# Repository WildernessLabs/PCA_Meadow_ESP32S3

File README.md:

# PCA_Meadow_ESP32S3
Meadow PCB using the ESP32 S3

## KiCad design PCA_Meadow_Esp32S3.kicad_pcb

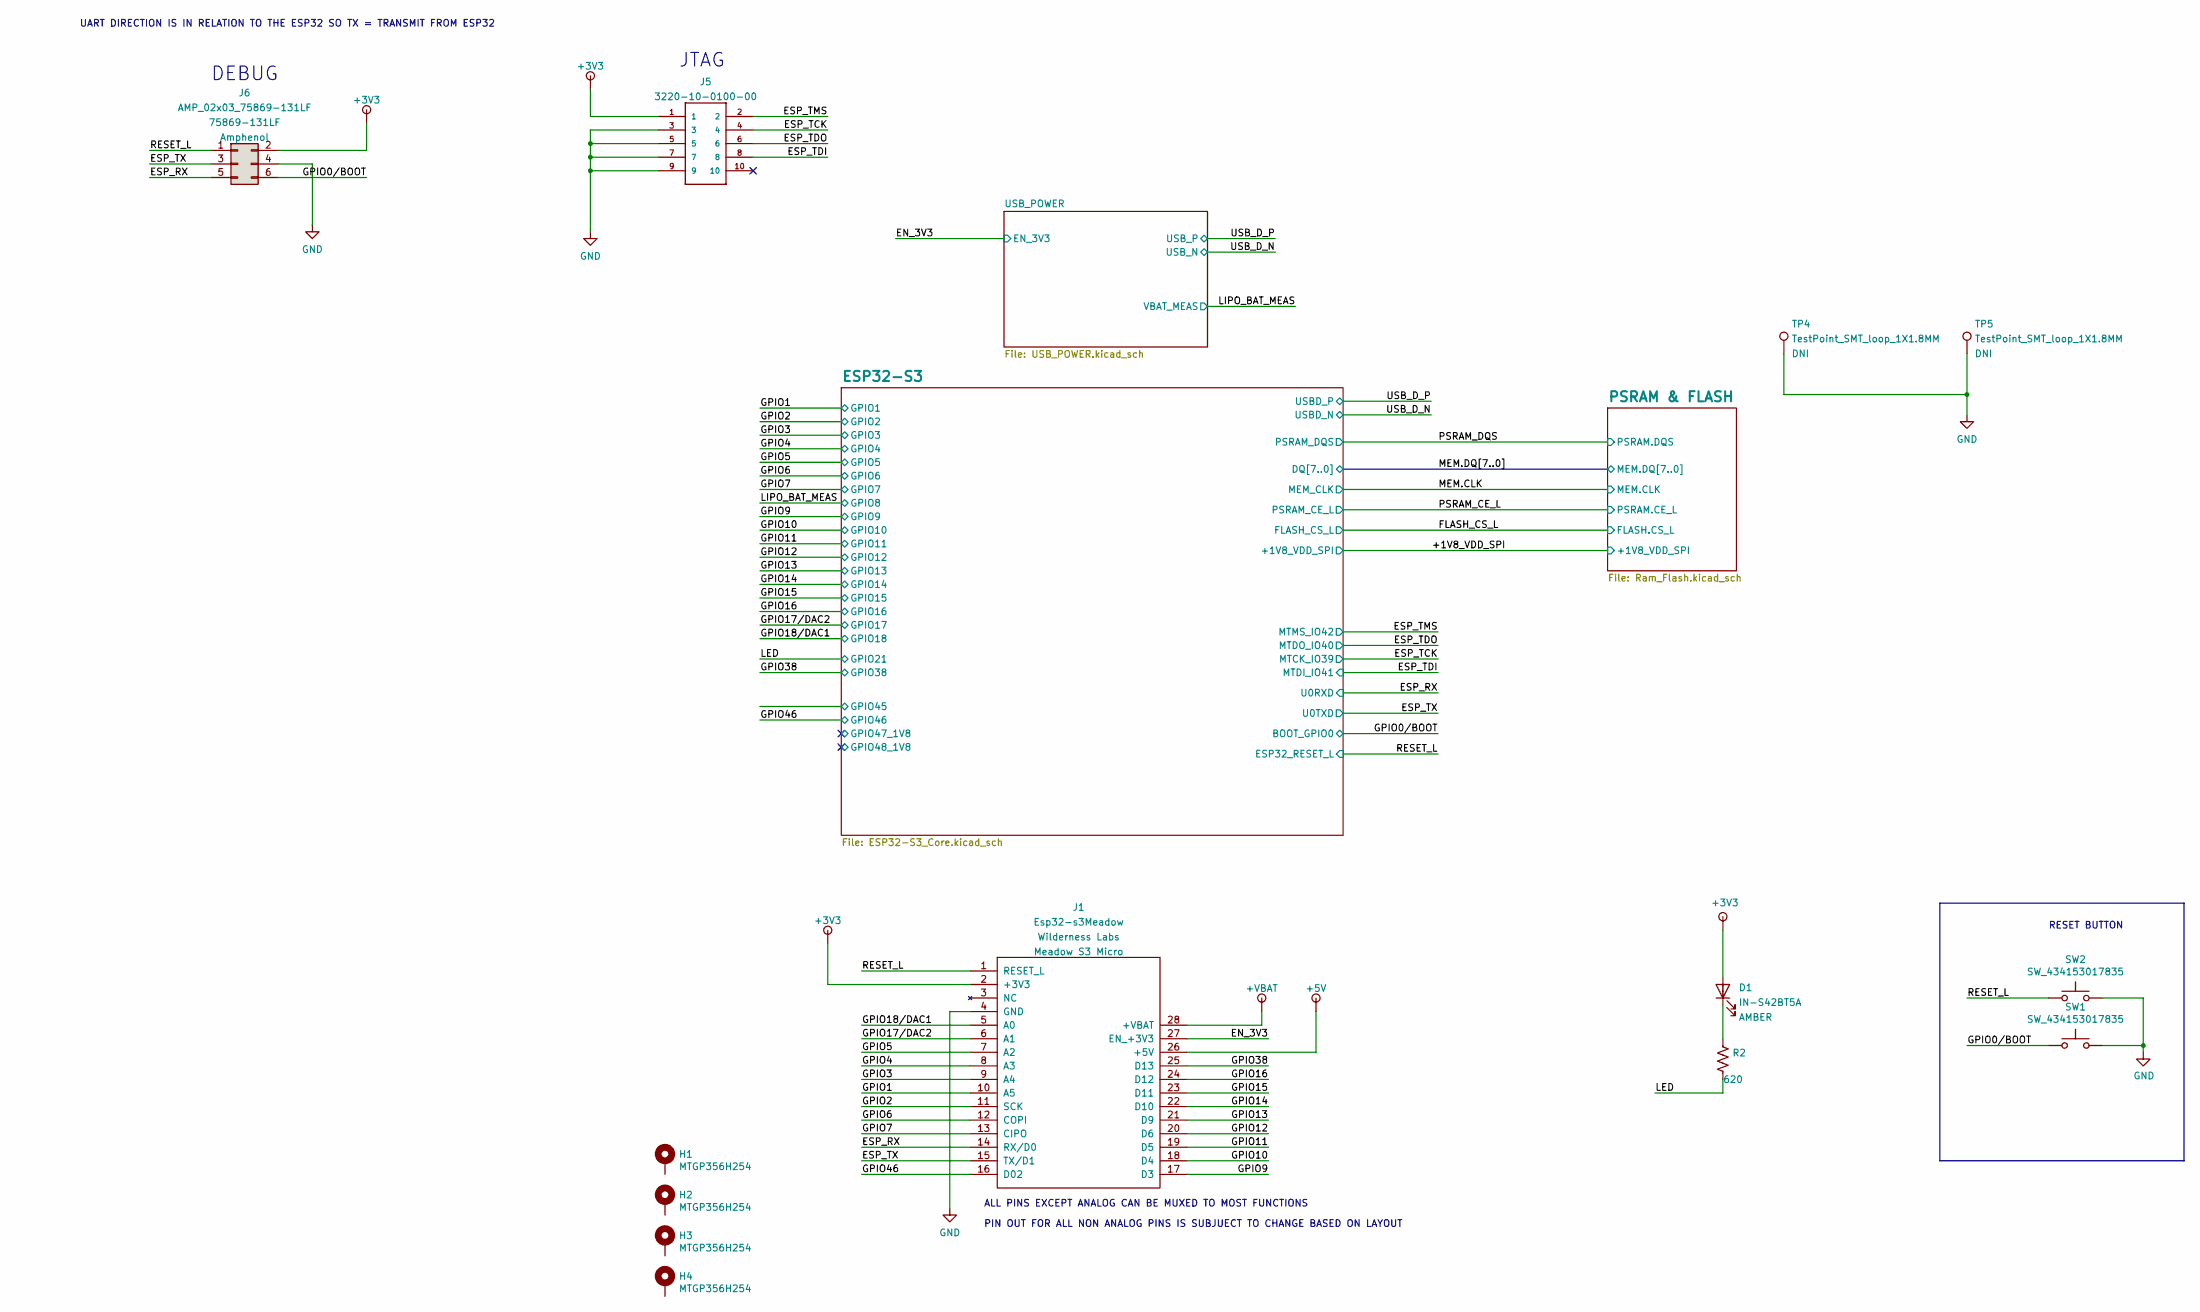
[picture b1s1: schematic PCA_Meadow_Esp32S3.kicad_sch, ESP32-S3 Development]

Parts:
D1: LED_A_IN-S42BT5A; LED_0402
H1, H2, H3, H4: MTGP356H254
J1: Esp32-s3Meadow; WL_S3_MicroMeadow
J5: CNC-3220-10-0100-00; CNC_3220-10-0100-00
J6: AMP_02x03_75869-131LF; Amphenol_75869-131LF
R2: R_620_1%_0201; R_0201
SW1, SW2: SW_434153017835; WURTH_434153017835
TP4, TP5: TestPoint_SMT_loop_1X1.8MM; TP_S2761-46R

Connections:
+3V3: D1.1 (A), J1.2 (+3V3), J5.1, J6.2; also elsewhere on the board
+5V: J1.26 (+5V); also elsewhere on the board
+VBAT: J1.28 (+VBAT); also elsewhere on the board
/EN_3V3: J1.27 (EN_+3V3); also elsewhere on the board
/ESP_RX: J1.14 (RX/D0), J6.5; also elsewhere on the board
/ESP_TCK: J5.4; also elsewhere on the board
/ESP_TDI: J5.8; also elsewhere on the board
/ESP_TDO: J5.6; also elsewhere on the board
/ESP_TMS: J5.2; also elsewhere on the board
/ESP_TX: J1.15 (TX/D1), J6.3; also elsewhere on the board
/GPIO0/BOOT: J6.6, SW1.1, SW1.3; also elsewhere on the board
/GPIO1: J1.10 (A5); also elsewhere on the board
/GPIO2: J1.11 (SCK); also elsewhere on the board
/GPIO3: J1.9 (A4); also elsewhere on the board
/GPIO4: J1.8 (A3); also elsewhere on the board
/GPIO5: J1.7 (A2); also elsewhere on the board
/GPIO6: J1.12 (COPI); also elsewhere on the board
/GPIO7: J1.13 (CIPO); also elsewhere on the board
/GPIO9: J1.17 (D3); also elsewhere on the board
/GPIO10: J1.18 (D4); also elsewhere on the board
/GPIO11: J1.19 (D5); also elsewhere on the board
/GPIO12: J1.20 (D6); also elsewhere on the board
/GPIO13: J1.21 (D9); also elsewhere on the board
/GPIO14: J1.22 (D10); also elsewhere on the board
/GPIO15: J1.23 (D11); also elsewhere on the board
/GPIO16: J1.24 (D12); also elsewhere on the board
/GPIO17/DAC2: J1.6 (A1); also elsewhere on the board
/GPIO18/DAC1: J1.5 (A0); also elsewhere on the board
/GPIO38: J1.25 (D13); also elsewhere on the board
/GPIO46: J1.16 (D02); also elsewhere on the board
/LED: R2.2; also elsewhere on the board
/RESET_L: J1.1 (RESET_L), J6.1, SW2.1, SW2.3; also elsewhere on the board
GND: J1.4 (GND), J5.3, J5.5, J5.7, J5.9, J6.4, SW1.2, SW1.4, SW2.2, SW2.4, TP4.1, TP5.1; also elsewhere on the board
unnamed: D1.2 (K), R2.1

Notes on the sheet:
UART DIRECTION IS IN RELATION TO THE ESP32 SO TX = TRANSMIT FROM ESP32
DEBUG
JTAG
RESET BUTTON
PIN OUT FOR ALL NON ANALOG PINS IS SUBJUECT TO CHANGE BASED ON LAYOUT
ALL PINS EXCEPT ANALOG CAN BE MUXED TO MOST FUNCTIONS

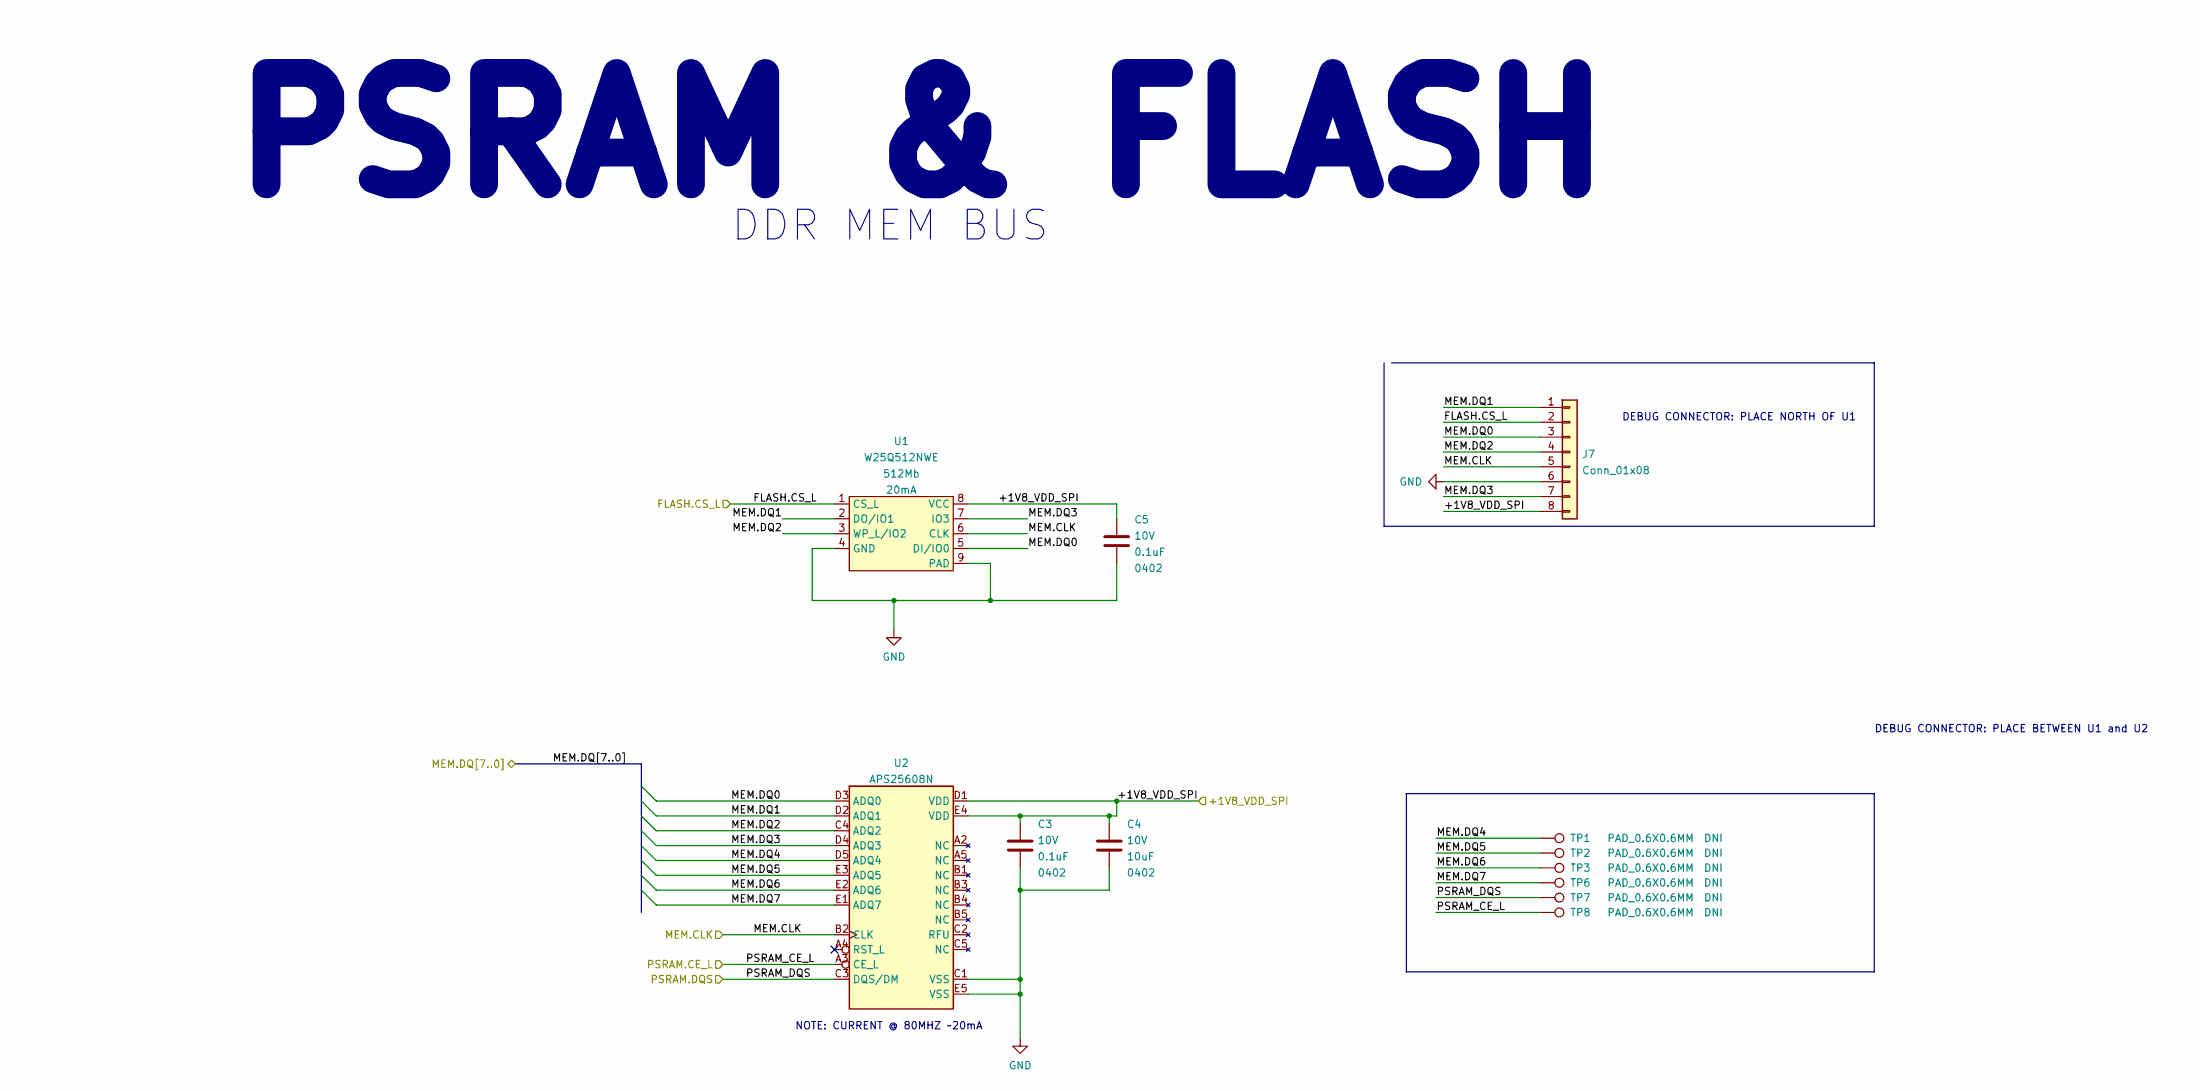
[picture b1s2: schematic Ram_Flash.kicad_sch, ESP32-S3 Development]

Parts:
C3, C5: C_0402_0.1UF_10V_X5R; C_0402_1005Metric; Voltage 10V; Tolerance 20%
C4: C_0402_10UF_10V_X5R; C_0402_1005Metric; Voltage 10V; Tolerance 20%
J7: Conn_01x08; PinHeader_2x04_P2.54mm_Vertical
TP1, TP2, TP3, TP6, TP7, TP8: PAD_0.6X0.6MM; PAD_SQ_0.6X0.6MM
U1: W25Q512NWE; WSON-8-1EP_6x8mm_P1.27mm_EP3.4x4.3mm; VOLTAGE 1.8V
U2: APS25608N; BGA24C100P5X5_800X600X120N

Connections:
/+1V8_VDD_SPI: C3.1, C4.1, C5.1, J7.8, U1.8 (VCC), U2.D1 (VDD), U2.E4 (VDD); also elsewhere on the board
/FLASH_CS_L: J7.2, U1.1 (CS_L); also elsewhere on the board
/MEM.CLK: J7.5, U1.6 (CLK), U2.B2 (CLK); also elsewhere on the board
/MEM.DQ0: J7.3, U1.5 (DI/IO0), U2.D3 (ADQ0); also elsewhere on the board
/MEM.DQ1: J7.1, U1.2 (DO/IO1), U2.D2 (ADQ1); also elsewhere on the board
/MEM.DQ2: J7.4, U1.3 (WP_L/IO2), U2.C4 (ADQ2); also elsewhere on the board
/MEM.DQ3: J7.7, U1.7 (IO3), U2.D4 (ADQ3); also elsewhere on the board
/MEM.DQ4: TP1.1, U2.D5 (ADQ4); also elsewhere on the board
/MEM.DQ5: TP2.1, U2.E3 (ADQ5); also elsewhere on the board
/MEM.DQ6: TP3.1, U2.E2 (ADQ6); also elsewhere on the board
/MEM.DQ7: TP6.1, U2.E1 (ADQ7); also elsewhere on the board
/PSRAM_CE_L: TP8.1, U2.A3 (CE_L); also elsewhere on the board
/PSRAM_DQS: TP7.1, U2.C3 (DQS/DM); also elsewhere on the board
GND: C3.2, C4.2, C5.2, J7.6, U1.4 (GND), U1.9 (PAD), U2.C1 (VSS), U2.E5 (VSS); also elsewhere on the board

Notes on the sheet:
DEBUG CONNECTOR: PLACE BETWEEN U1 and U2
DEBUG CONNECTOR: PLACE NORTH OF U1
NOTE: CURRENT @ 80MHZ ~20mA
PSRAM & FLASH
DDR MEM BUS

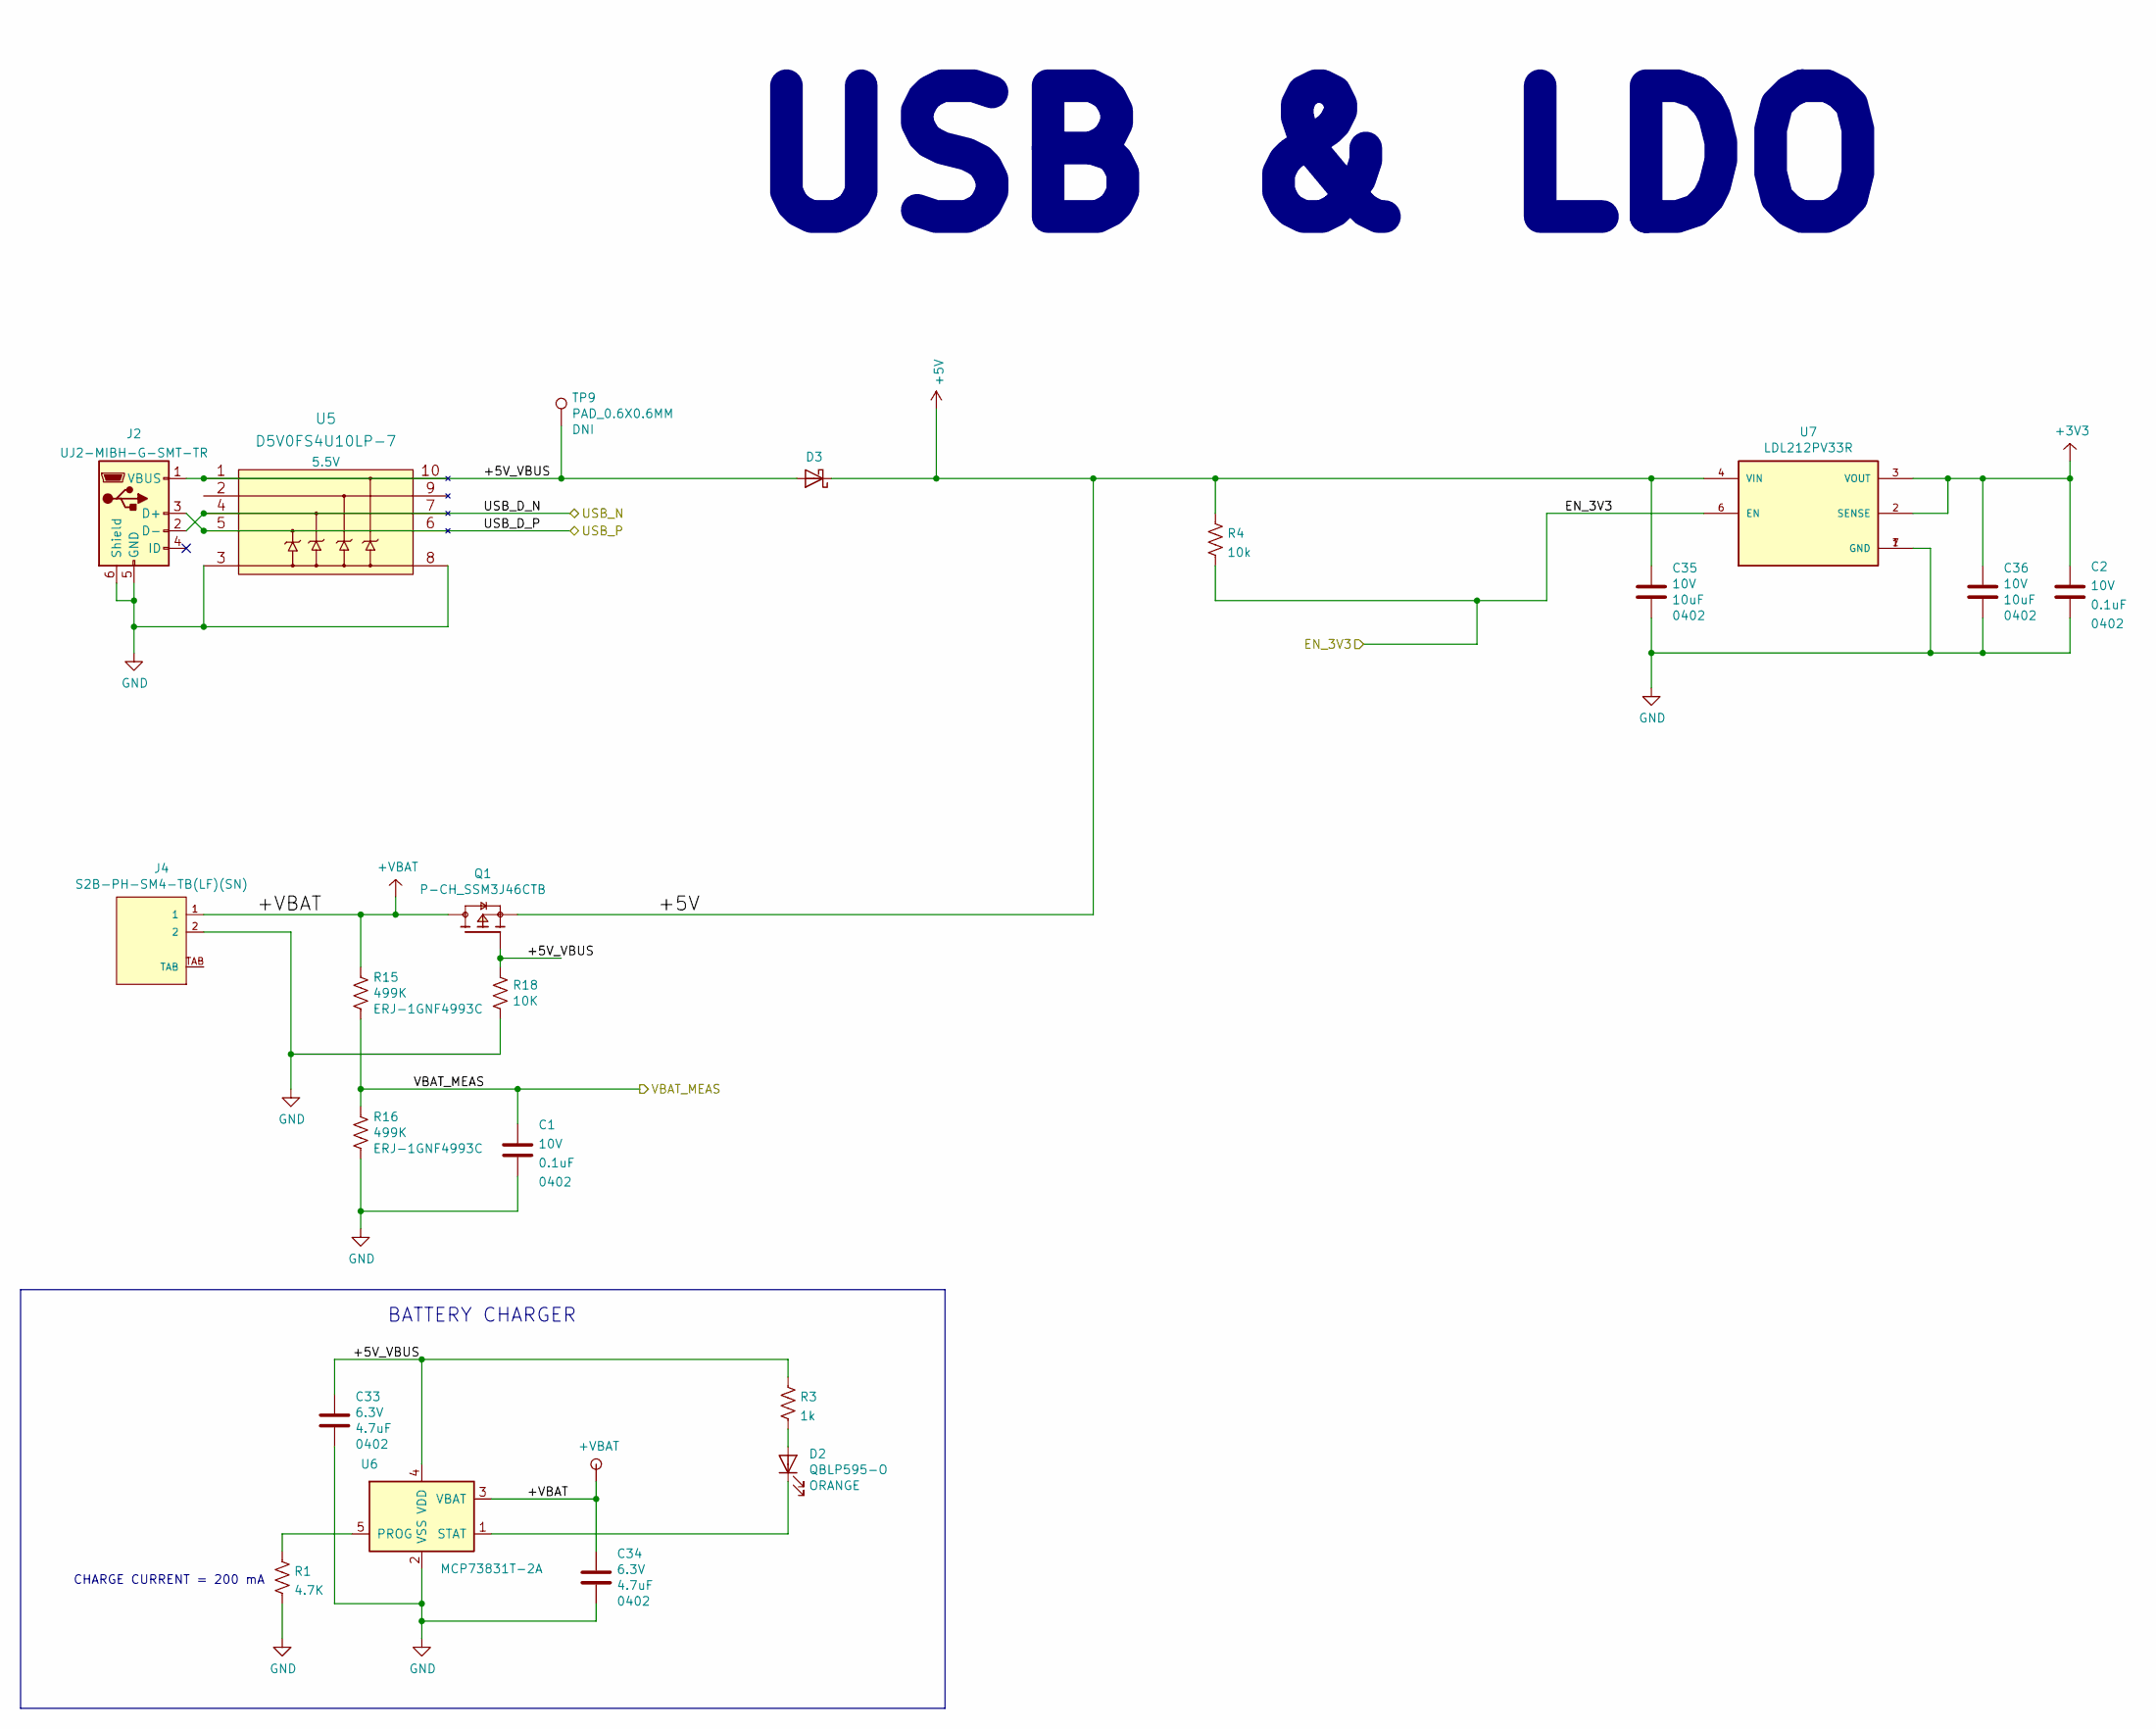
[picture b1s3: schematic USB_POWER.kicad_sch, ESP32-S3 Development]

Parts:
C1, C2: C_0402_0.1UF_10V_X5R; C_0402_1005Metric; Voltage 10V; Tolerance 20%
C33, C34: C_0402_4.7UF_10V_X5R_10%; C_0402_1005Metric; Voltage 6.3V; Tolerance 10%
C35, C36: C_0402_10UF_10V_X5R; C_0402_1005Metric; Voltage 10V; Tolerance 20%
D2: LED_O_QBLP595-O; LED_0402
D3: BAT60A; D_SOD-323
J2: USB_B_MicroCUI; USB_Micro-B_CUI_UJ2-MIBH-G
J4: S2B-PH-SM4-TB(LF)(SN); JST_S2B-PH-SM4-TB(LF)(SN)
Q1: P-CH_SSM3J46CTB; CST3b_TOS
R1: R_4K7_1%_0402; R_0402_1005Metric
R3: R_1K_1%_0402; R_0402_1005Metric; Tolerance 1%
R4: R_10k_1%_0603; R_0603; Tolerance 1%
R15, R16: R_499K_1%_0201; R_0201
R18: R_10K_1%_0201; R_0201
TP9: PAD_0.6X0.6MM; PAD_SQ_0.6X0.6MM
U5: D5V0FS4U10LP-7; U-DFN2510_1X2P5_DIO; Voltage 5.5V
U6: MCP73831T-2A; SOT-23-5
U7: LDL212PV33R; SON50P200X200X80-7N

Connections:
+3V3: C2.1, C36.1, U7.2 (SENSE), U7.3 (VOUT); also elsewhere on the board
+5V: C35.1, D3.1 (K), Q1.2 (SOURCE), R4.1, U7.4 (VIN); also elsewhere on the board
+VBAT: C34.1, J4.1, Q1.3 (DRAIN), R15.1, U6.3 (VBAT); also elsewhere on the board
/EN_3V3: R4.2, U7.6 (EN); also elsewhere on the board
/LIPO_BAT_MEAS: C1.1, R15.2, R16.1; also elsewhere on the board
/USB_D_N: J2.2 (D-), U5.4; also elsewhere on the board
/USB_D_P: J2.3 (D+), U5.5; also elsewhere on the board
/USB_POWER/+5V_VBUS: C33.1, D3.2 (A), J2.1 (VBUS), Q1.1 (GATE), R3.1, R18.1, TP9.1, U5.1, U6.4 (VDD)
GND: C1.2, C2.2, C33.2, C34.2, C35.2, C36.2, J2.5 (GND), J2.6 (Shield), J4.2, R1.2, R16.2, R18.2, U5.3 (VSS), U5.8 (VSS), U6.2 (VSS), U7.1 (GND), U7.7 (GND); also elsewhere on the board
unnamed: D2.1 (A), R3.2
unnamed: D2.2 (K), U6.1 (STAT)
unnamed: R1.1, U6.5 (PROG)

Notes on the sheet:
CHARGE CURRENT = 200 mA
USB & LDO
BATTERY CHARGER

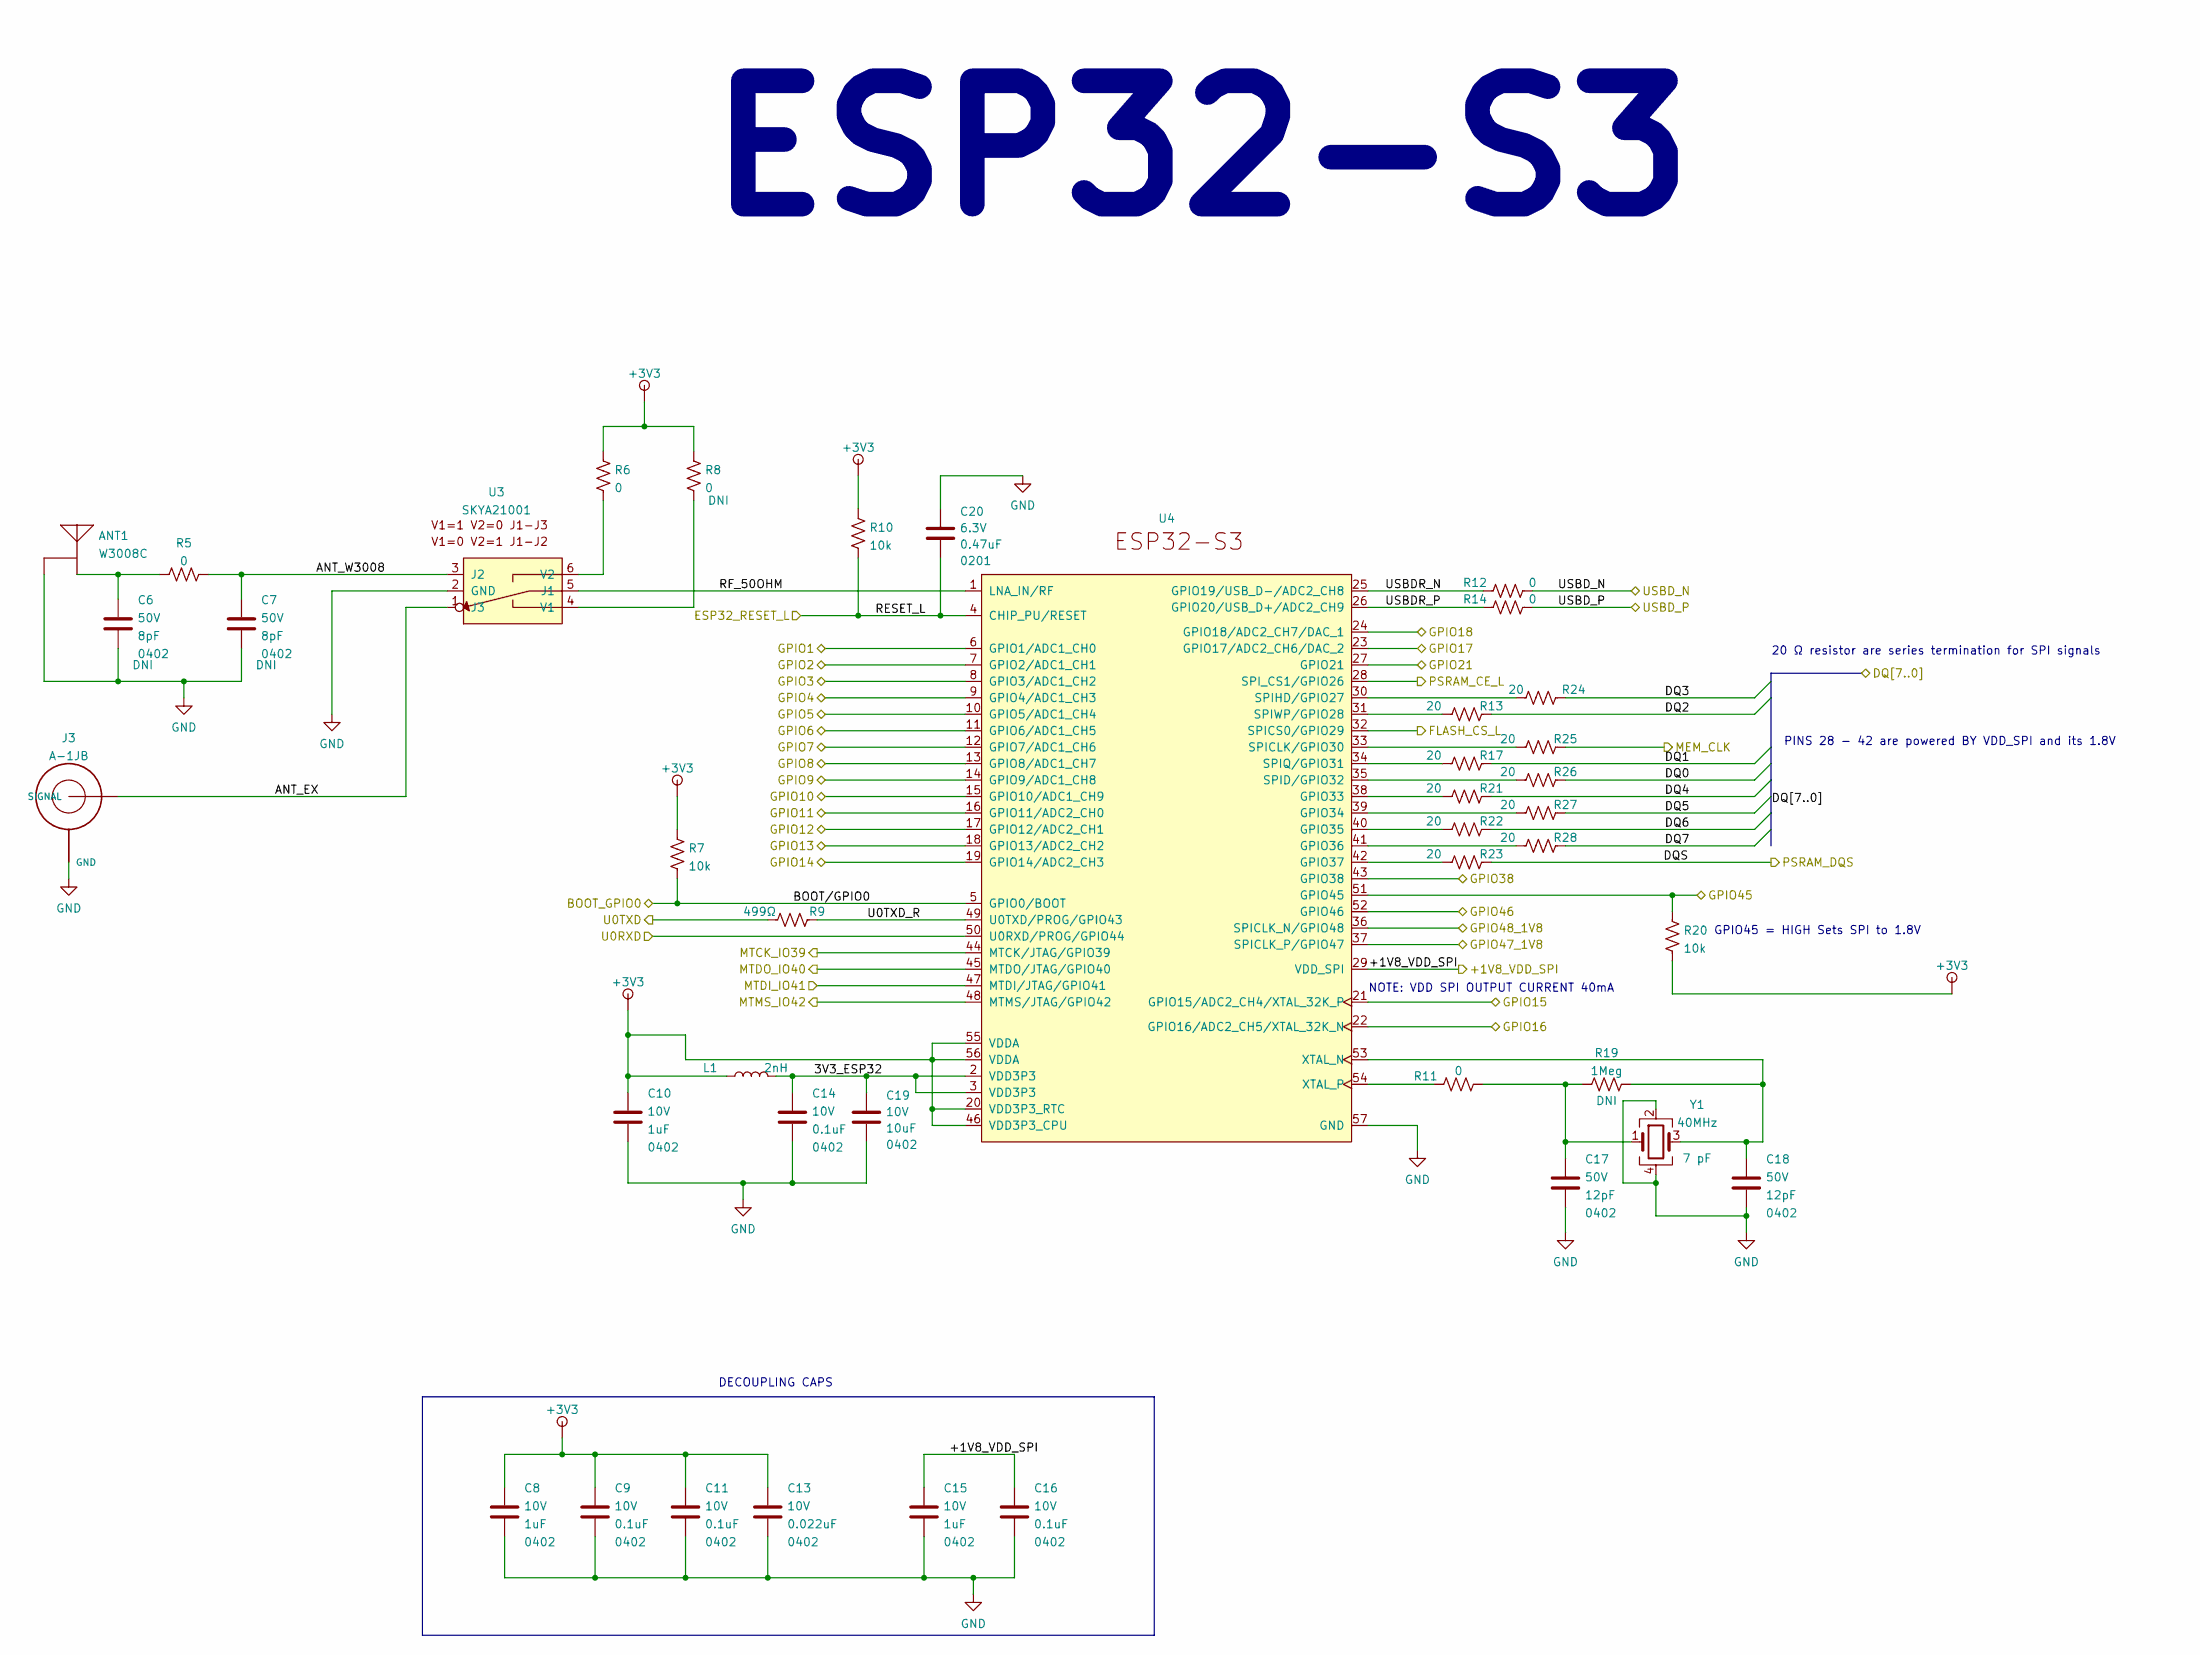
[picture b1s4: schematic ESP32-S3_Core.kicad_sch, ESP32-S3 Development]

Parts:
ANT1: W3008C; ANTENNA_W3008C
C6, C7: C_0402_8pF_50V_X5R; C_0402_1005Metric; Voltage 50V; Tolerance 0.25pF
C8, C10, C15: C_0402_1UF_10V_X5R; C_0402_1005Metric; Voltage 10V; Tolerance 20%
C9, C11, C14, C16: C_0402_0.1UF_10V_X5R; C_0402_1005Metric; Voltage 10V; Tolerance 20%
C13: C_0402_0.022UF_50V_X5R; C_0402_1005Metric; Voltage 10V; Tolerance 10%
C17, C18: C_0402_12pF_50V_X5R; C_0402_1005Metric; Voltage 50V; Tolerance 5%
C19: C_0402_10UF_10V_X5R; C_0402_1005Metric; Voltage 10V; Tolerance 20%
C20: C_0201_0.47UF_6.3V_X5R; C_0201; Voltage 6.3V; Tolerance 10%
J3: A-1JB; AMPHENOL_A-1JB
L1: L_0402_2nH_50mΩ; L_0402; I Rating 1A; PartValue 2nH
R5, R11, R12, R14: R_0_1%_0402; R_0402_1005Metric
R6, R8: R_0R_1%_0603; R_0603; Tolerance 1%
R7, R10, R20: R_10k_1%_0603; R_0603; Tolerance 1%
R9: R_499R_1%_0603; R_0603; Tolerance 1%
R13, R17, R21, R22, R23, R24, R25, R26, R27, R28: R_20_1%_0402; R_0402_1005Metric
R19: R_1M_1%_0402; R_0402_1005Metric
U3: SKYA21001; SOT-363_SC-70-6
U4: ESP32-S3; QFN-56_EP_7x7_Pitch0.4mm
Y1: ABM12W-40.0000MHZ-7-B1U-T3; XTAL_ABM12W-24.0000MHZ-6-B1U-T3

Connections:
+3V3: C8.1, C9.1, C10.1, C11.1, C13.1, L1.1, R6.1, R7.1, R8.1, R10.1, R20.2, U4.20 (VDD3P3_RTC), U4.46 (VDD3P3_CPU), U4.55 (VDDA), U4.56 (VDDA); also elsewhere on the board
/+1V8_VDD_SPI: C15.1, C16.1, U4.29 (VDD_SPI); also elsewhere on the board
/ESP32-S3/3V3_ESP32: C14.1, C19.1, L1.2, U4.2 (VDD3P3), U4.3 (VDD3P3)
/ESP32-S3/ANT_EX: J3.SIGNAL, U3.1 (J3)
/ESP32-S3/ANT_W3008: C7.1, R5.2, U3.3 (J2)
/ESP32-S3/GPIO45: R20.1, U4.51 (GPIO45)
/ESP32-S3/GPIO47_1V8: U4.37 (SPICLK_P/GPIO47)
/ESP32-S3/GPIO48_1V8: U4.36 (SPICLK_N/GPIO48)
/ESP32-S3/RF_50OHM: U3.5 (J1), U4.1 (LNA_IN/RF)
/ESP32-S3/U0TXD_R: R9.2, U4.49 (U0TXD/PROG/GPIO43)
/ESP32-S3/USBDR_N: R12.1, U4.25 (GPIO19/USB_D-/ADC2_CH8)
/ESP32-S3/USBDR_P: R14.1, U4.26 (GPIO20/USB_D+/ADC2_CH9)
/ESP_RX: U4.50 (U0RXD/PROG/GPIO44); also elsewhere on the board
/ESP_TCK: U4.44 (MTCK/JTAG/GPIO39); also elsewhere on the board
/ESP_TDI: U4.47 (MTDI/JTAG/GPIO41); also elsewhere on the board
/ESP_TDO: U4.45 (MTDO/JTAG/GPIO40); also elsewhere on the board
/ESP_TMS: U4.48 (MTMS/JTAG/GPIO42); also elsewhere on the board
/ESP_TX: R9.1; also elsewhere on the board
/FLASH_CS_L: U4.32 (SPICS0/GPIO29); also elsewhere on the board
/GPIO0/BOOT: R7.2, U4.5 (GPIO0/BOOT); also elsewhere on the board
/GPIO1: U4.6 (GPIO1/ADC1_CH0); also elsewhere on the board
/GPIO2: U4.7 (GPIO2/ADC1_CH1); also elsewhere on the board
/GPIO3: U4.8 (GPIO3/ADC1_CH2); also elsewhere on the board
/GPIO4: U4.9 (GPIO4/ADC1_CH3); also elsewhere on the board
/GPIO5: U4.10 (GPIO5/ADC1_CH4); also elsewhere on the board
/GPIO6: U4.11 (GPIO6/ADC1_CH5); also elsewhere on the board
/GPIO7: U4.12 (GPIO7/ADC1_CH6); also elsewhere on the board
/GPIO9: U4.14 (GPIO9/ADC1_CH8); also elsewhere on the board
/GPIO10: U4.15 (GPIO10/ADC1_CH9); also elsewhere on the board
/GPIO11: U4.16 (GPIO11/ADC2_CH0); also elsewhere on the board
/GPIO12: U4.17 (GPIO12/ADC2_CH1); also elsewhere on the board
/GPIO13: U4.18 (GPIO13/ADC2_CH2); also elsewhere on the board
/GPIO14: U4.19 (GPIO14/ADC2_CH3); also elsewhere on the board
/GPIO15: U4.21 (GPIO15/ADC2_CH4/XTAL_32K_P); also elsewhere on the board
/GPIO16: U4.22 (GPIO16/ADC2_CH5/XTAL_32K_N); also elsewhere on the board
/GPIO17/DAC2: U4.23 (GPIO17/ADC2_CH6/DAC_2); also elsewhere on the board
/GPIO18/DAC1: U4.24 (GPIO18/ADC2_CH7/DAC_1); also elsewhere on the board
/GPIO38: U4.43 (GPIO38); also elsewhere on the board
/GPIO46: U4.52 (GPIO46); also elsewhere on the board
/LED: U4.27 (GPIO21); also elsewhere on the board
/LIPO_BAT_MEAS: U4.13 (GPIO8/ADC1_CH7); also elsewhere on the board
/MEM.CLK: R25.2; also elsewhere on the board
/MEM.DQ0: R26.2; also elsewhere on the board
/MEM.DQ1: R17.2; also elsewhere on the board
/MEM.DQ2: R13.2; also elsewhere on the board
/MEM.DQ3: R24.2; also elsewhere on the board
/MEM.DQ4: R21.2; also elsewhere on the board
/MEM.DQ5: R27.2; also elsewhere on the board
/MEM.DQ6: R22.2; also elsewhere on the board
/MEM.DQ7: R28.2; also elsewhere on the board
/PSRAM_CE_L: U4.28 (SPI_CS1/GPIO26); also elsewhere on the board
/PSRAM_DQS: R23.2; also elsewhere on the board
/RESET_L: C20.2, R10.2, U4.4 (CHIP_PU/RESET); also elsewhere on the board
/USB_D_N: R12.2; also elsewhere on the board
/USB_D_P: R14.2; also elsewhere on the board
GND: ANT1.G1 (GND), ANT1.G2 (GND), C6.2, C7.2, C8.2, C9.2, C10.2, C11.2, C13.2, C14.2, C15.2, C16.2, C17.2, C18.2, C19.2, C20.1, J3.GND1 (GND), J3.GND2 (GND), J3.OPTIONAL_GND (GND), U3.2 (GND), U4.57 (GND), Y1.2, Y1.4; also elsewhere on the board
unnamed: ANT1.FEED, C6.1, R5.1
unnamed: C17.1, R11.2, R19.1, Y1.1
unnamed: C18.1, R19.2, U4.53 (XTAL_N), Y1.3
unnamed: R6.2, U3.6 (V2)
unnamed: R8.2, U3.4 (V1)
unnamed: R11.1, U4.54 (XTAL_P)
unnamed: R13.1, U4.31 (SPIWP/GPIO28)
unnamed: R17.1, U4.34 (SPIQ/GPIO31)
unnamed: R21.1, U4.38 (GPIO33)
unnamed: R22.1, U4.40 (GPIO35)
unnamed: R23.1, U4.42 (GPIO37)
unnamed: R24.1, U4.30 (SPIHD/GPIO27)
unnamed: R25.1, U4.33 (SPICLK/GPIO30)
unnamed: R26.1, U4.35 (SPID/GPIO32)
unnamed: R27.1, U4.39 (GPIO34)
unnamed: R28.1, U4.41 (GPIO36)

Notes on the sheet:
20 Ω resistor are series termination for SPI signals
ESP32-S3
NOTE: VDD SPI OUTPUT CURRENT 40mA
PINS 28 - 42 are powered BY VDD_SPI and its 1.8V
DECOUPLING CAPS
GPIO45 = HIGH Sets SPI to 1.8V

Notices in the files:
parts and their libraries:
Copyright 2016 Accelerated Designs. All rights reserved.
